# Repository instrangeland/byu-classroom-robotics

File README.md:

# BYU Classroom Robotics

## Introduction

Welcome to the **BYU Classroom Robotics** project. It was built for the as a 2024 Immerse Broader Impacts Project by Ethan Hunter and Ephraim.

It utelizes a Rpi Pico for the main board and ESP32s for the controllers. Many features should move over to any other micropython based board, though the actual boards would need redesign. 

Most of the files are not used in the actual robots! They are simply there as documenting the journey, and maybe helping give some basic examples for how to use some of the libraries. 

The two you'll want to look at is main.py, for the main board and controller.py. Each board will also need to have ble_advertising.py copied to the board. The joystick will need joystick_channel.py as well. 

The controller allows switching between tank drive & one joystick driving. The default is tank drive. It displays an animation when switching on the controller. 

Each controller must be assigned a number. Make sure to put a file called "dev_name" with the number on the flash as well. When the controller and the robot connect, they will both light up the controller number in binary on the included LEDs.

The pairing is only... partially done. There's a few options I see for it now. Currently, the pairing code only really allows for one controller + one robot. I never got around to rewriting the bluetooth scan code for it to find a list of all bluetooth devices and than iterate thru them. The way I see it working is that the main board is constantly advertising how many connections it has. The controllers will cycle thru all available connections. When it connects to one, it checks to see if it has 1 or 0 connections. Then it waits a random amount of time, and then if it still says it's only connected to one, it "locks in." If another one is connected after that time, it flips a coin, 25% it switches. If it doesn't switch, it waits a random amount of time, and then switches again. Overall, they should all find their own connections eventually. It is already set up to transmit the controller number, and the main board transmits how many devices are connected. 

The main board uses a seperate smaller board for the LEDs. The controller has them built in.

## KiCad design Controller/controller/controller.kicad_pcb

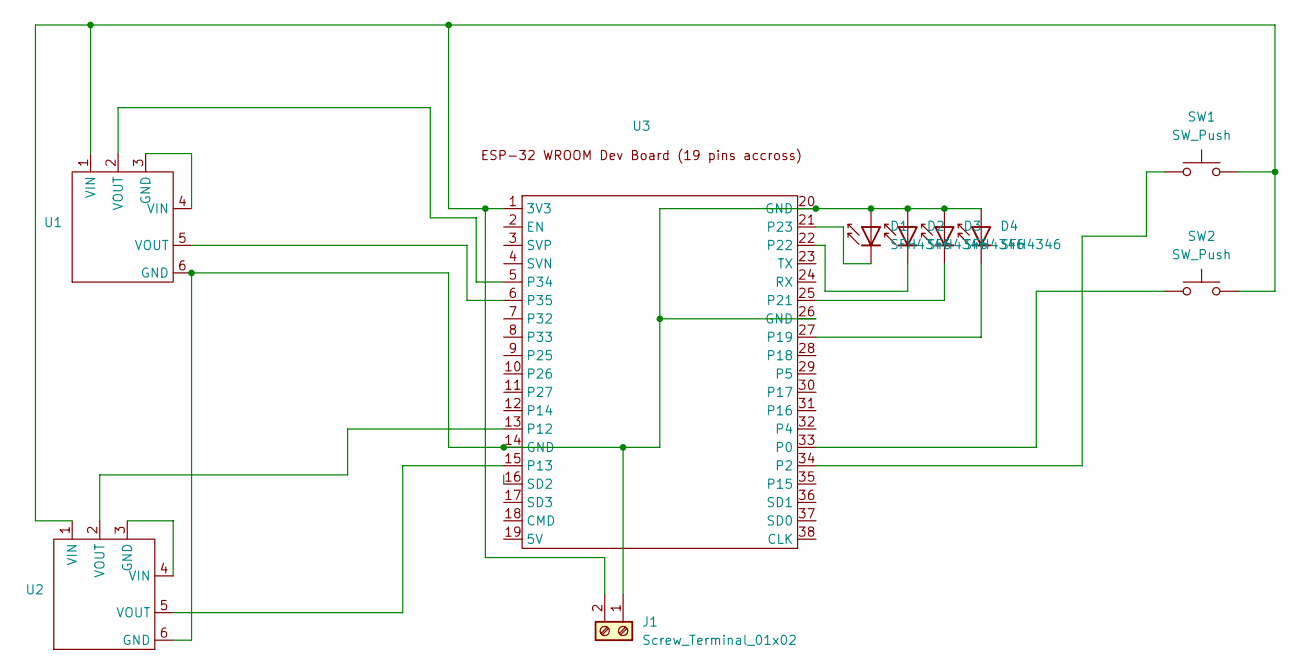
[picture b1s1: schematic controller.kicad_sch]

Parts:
D1, D2, D3, D4: SFH4346; LED_D3.0mm_IRBlack
J1: Screw_Terminal_01x02; 2 wide through hole .5cm
SW1, SW2: SW_Push; SW_Push_1P1T_NO_CK_PTS125Sx43PSMTR
U1, U2: B10k-1
U3: ESP32-wroom

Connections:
unnamed: D1.2 (A), D2.2 (A), D3.2 (A), D4.2 (A), J1.1, U1.6 (GND), U2.6 (GND), U3.14 (GND), U3.20 (GND), U3.26 (GND)
unnamed: D1.1 (K), U3.21 (P23)
unnamed: D2.1 (K), U3.22
unnamed: D3.1 (K), U3.25 (P21)
unnamed: D4.1 (K), U3.27 (P19)
unnamed: J1.2, SW1.2, SW2.2, U1.1 (VIN), U2.1 (VIN), U3.1 (3V3)
unnamed: U1.3 (GND), U1.4 (VIN)
unnamed: U2.3 (GND), U2.4 (VIN)
unnamed: SW2.1, U3.33 (P0)
unnamed: SW1.1, U3.34 (P2)
unnamed: U2.2 (VOUT), U3.13 (P12)
unnamed: U2.5 (VOUT), U3.15 (P13)
unnamed: U1.2 (VOUT), U3.5 (P34)
unnamed: U1.5 (VOUT), U3.6 (P35)

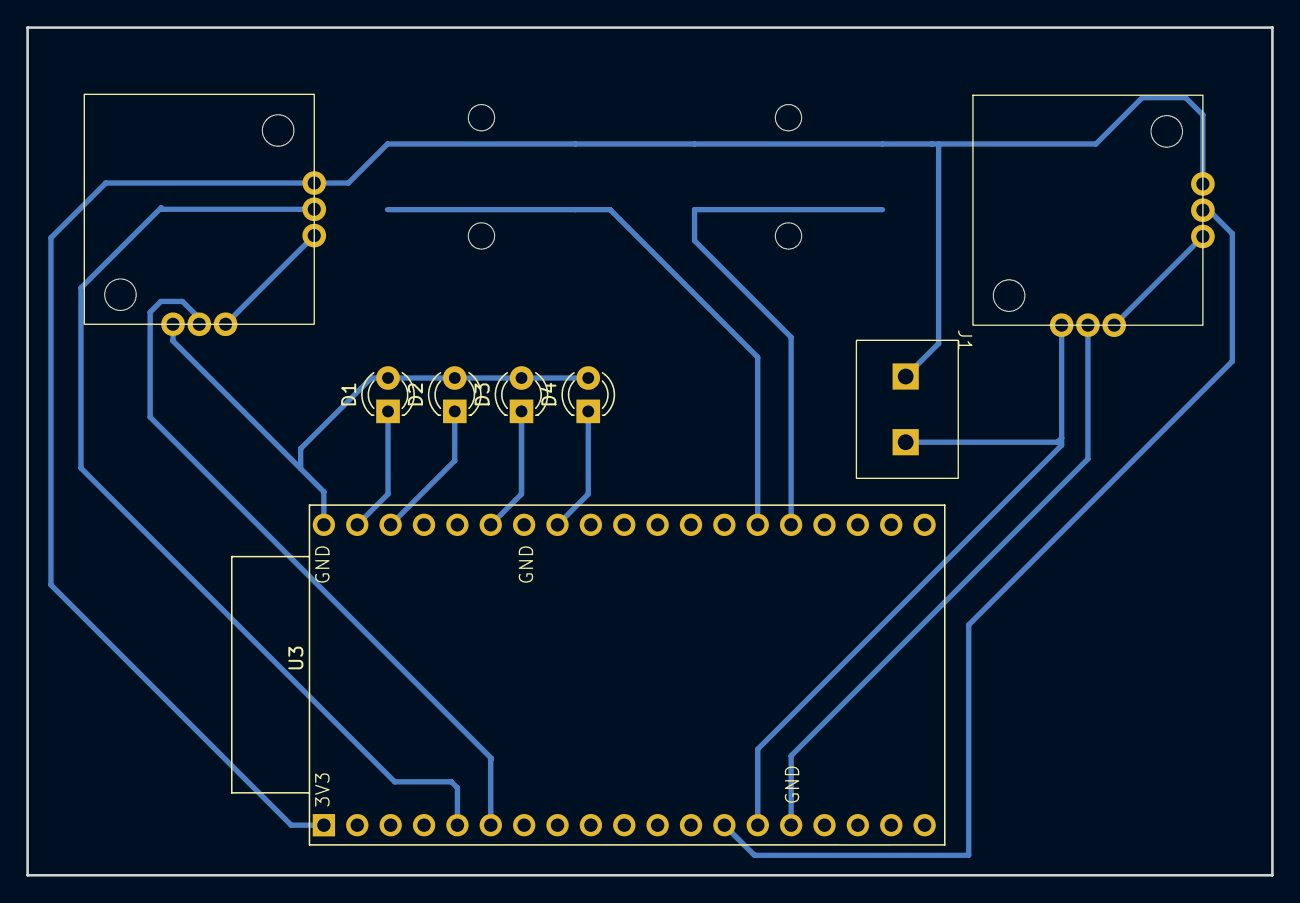
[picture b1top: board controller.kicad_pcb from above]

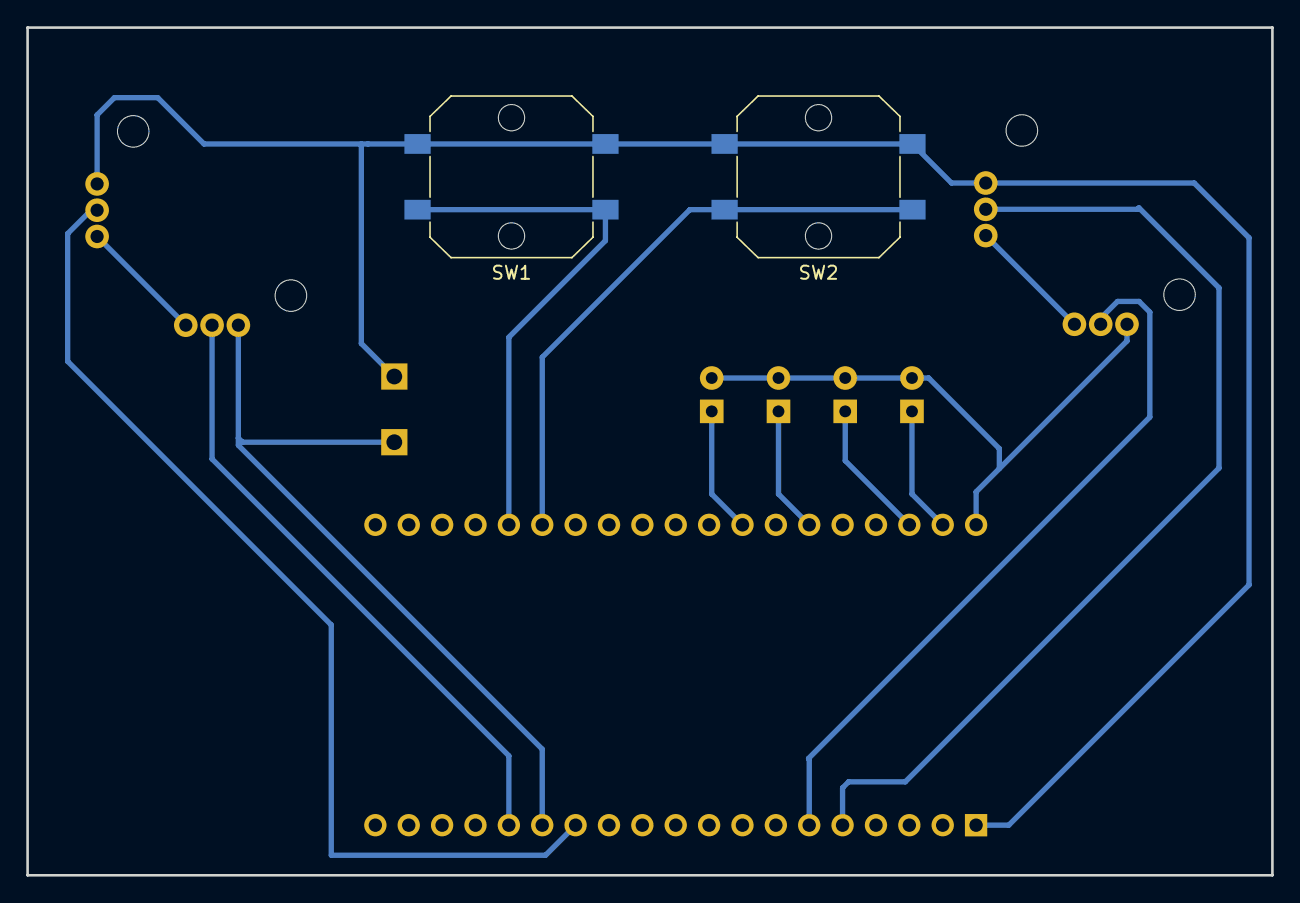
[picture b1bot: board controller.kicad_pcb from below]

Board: 2 copper layers, 94.7 x 64.5 mm, 10 parts (2 on the bottom side), 14 nets.

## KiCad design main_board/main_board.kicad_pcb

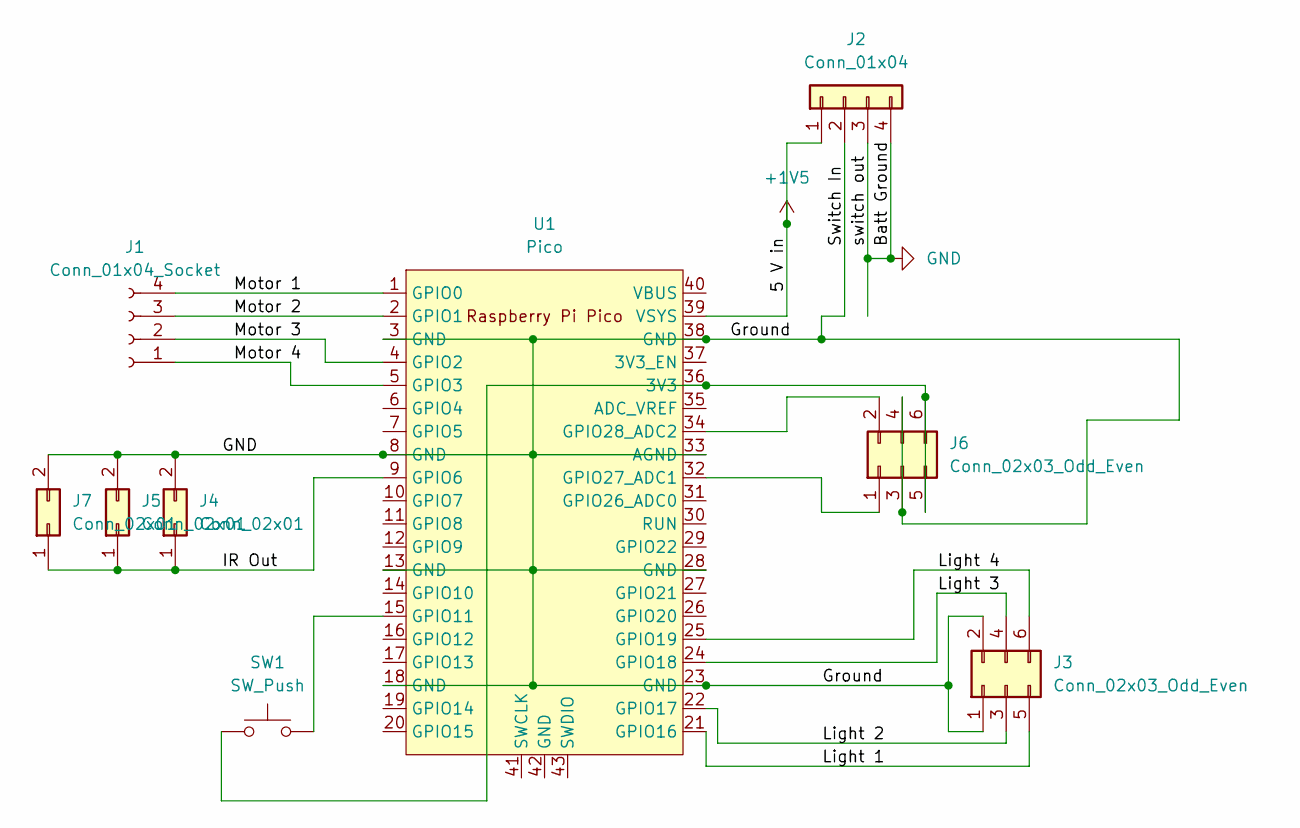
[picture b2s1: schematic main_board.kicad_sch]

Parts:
J1: Conn_01x04_Socket; PinHeader_1x04_P2.54mm_Vertical
J2: Conn_01x04; PinHeader_1x04_P2.54mm_Vertical
J3, J6: Conn_02x03_Odd_Even; PinHeader_2x03_P2.54mm_Vertical
J4, J5, J7: Conn_02x01; PinHeader_2x01_P2.54mm_Vertical
SW1: SW_Push; SW_Push_1P1T_NO_CK_PTS125Sx43PSMTR
U1: Pico; RPi_Pico_SMD_TH

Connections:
+1V5: J2.1, U1.39 (VSYS)
/IR Out: J4.1, J5.1, J7.1, U1.9 (GPIO6)
/Light 1: J3.5, U1.21 (GPIO16)
/Light 2: J3.3, U1.22 (GPIO17)
/Light 3: J3.4, U1.24 (GPIO18)
/Light 4: J3.6, U1.25 (GPIO19)
/Motor 1: J1.4, U1.1 (GPIO0)
/Motor 2: J1.3, U1.2 (GPIO1)
/Motor 3: J1.2, U1.4 (GPIO2)
/Motor 4: J1.1, U1.5 (GPIO3)
GND: J2.2, J2.3, J2.4, J3.1, J3.2, J4.2, J5.2, J6.3, J6.4, J7.2, U1.3 (GND), U1.8 (GND), U1.13 (GND), U1.18 (GND), U1.23 (GND), U1.28 (GND), U1.33 (AGND), U1.38 (GND)
unnamed: J6.1, U1.32 (GPIO27_ADC1)
unnamed: J6.2, U1.34 (GPIO28_ADC2)
unnamed: J6.5, J6.6, SW1.1, U1.36 (3V3)
unnamed: SW1.2, U1.15 (GPIO11)

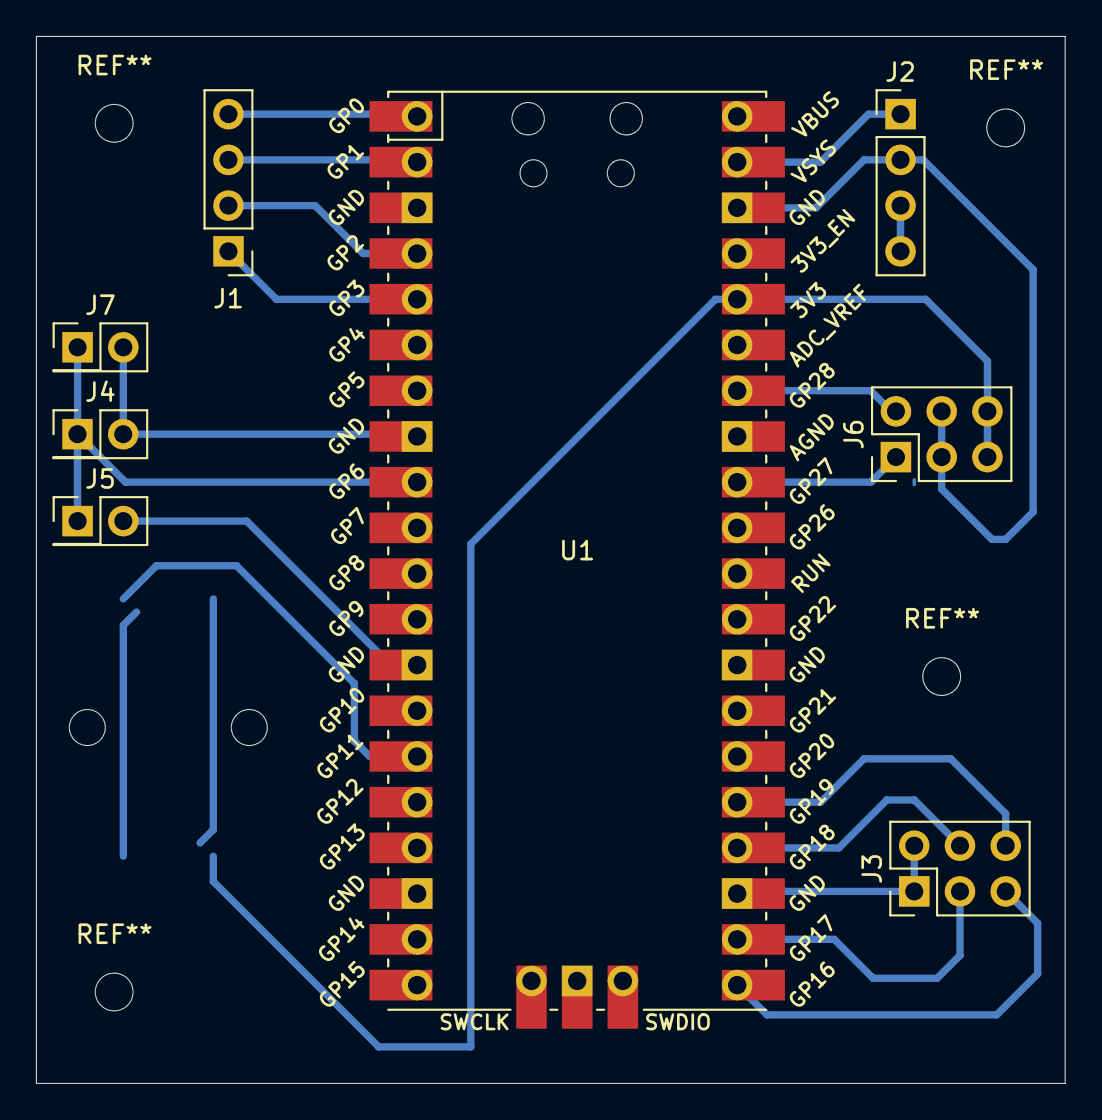
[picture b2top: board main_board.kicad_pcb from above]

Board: 2 copper layers, 57.1 x 58.2 mm, 9 parts (1 on the bottom side), 15 nets.

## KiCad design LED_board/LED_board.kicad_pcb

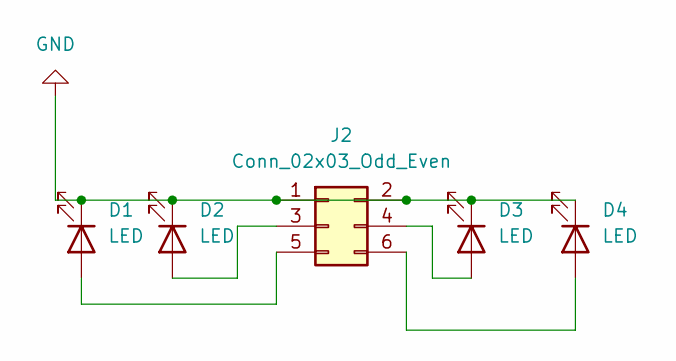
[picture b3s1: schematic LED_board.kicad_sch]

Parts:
D1, D2, D3, D4: LED; big_led
J2: Conn_02x03_Odd_Even; PinHeader_2x03_P2.54mm_Vertical

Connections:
GND: D1.1 (K), D2.1 (K), D3.1 (K), D4.1 (K), J2.1, J2.2
unnamed: D1.2 (A), J2.5
unnamed: D2.2 (A), J2.3
unnamed: D3.2 (A), J2.4
unnamed: D4.2 (A), J2.6

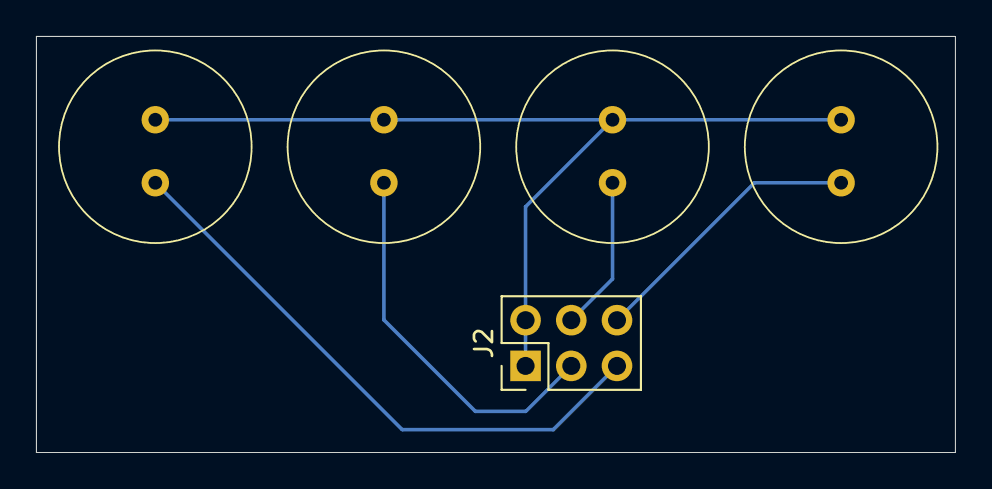
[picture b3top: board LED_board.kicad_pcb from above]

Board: 2 copper layers, 51.1 x 23.1 mm, 5 parts (0 on the bottom side), 5 nets.
